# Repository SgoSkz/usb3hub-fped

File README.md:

# usb3hub-fped USB 3 Hub for Programmers &amp; Embedded Developers

## What's wrong with normal USB hubs? **Nothing**. USB hubs have tons of
features like an SD reader, HDMI/DP output (video), EXTRA USB PORTS (shocking),
and sometimes even audio jacks. These are all great features, _but_ I want a
USB hub that has features for embedded programming such as i2c, spi, uart, and
maybe even jtag (prob not). Mainly because I'm tired of having 4 different
devices for dealing with one project.

## Goals
- [ ] Basic USB hub functional
- [ ] SD card reader
- [ ] Embedded programmer stuff functional

## Plan
- 3x USB 3 downstream ports available
- 1x USB 3 downstream reserved for USB 2 hub
- USB 2 hub connects to embedded programming devices and SD reader

## Hardware
- Utilizes the TUSB8041
- Embedded stuff
	- Possibly put an ATmega32u4
		- Easy to program with native USB support
	- Individual IC's for i2c, spi, uart, etc
	- Other IC/uC
- Power management ICs
	- 1v1	->
	- 3v3	->
	- 5v	->
- XTAL selection
	- 24MHz	->

## Software
- Developed in KiCAD :D

## License Here When Chosen
- Ermmm =T

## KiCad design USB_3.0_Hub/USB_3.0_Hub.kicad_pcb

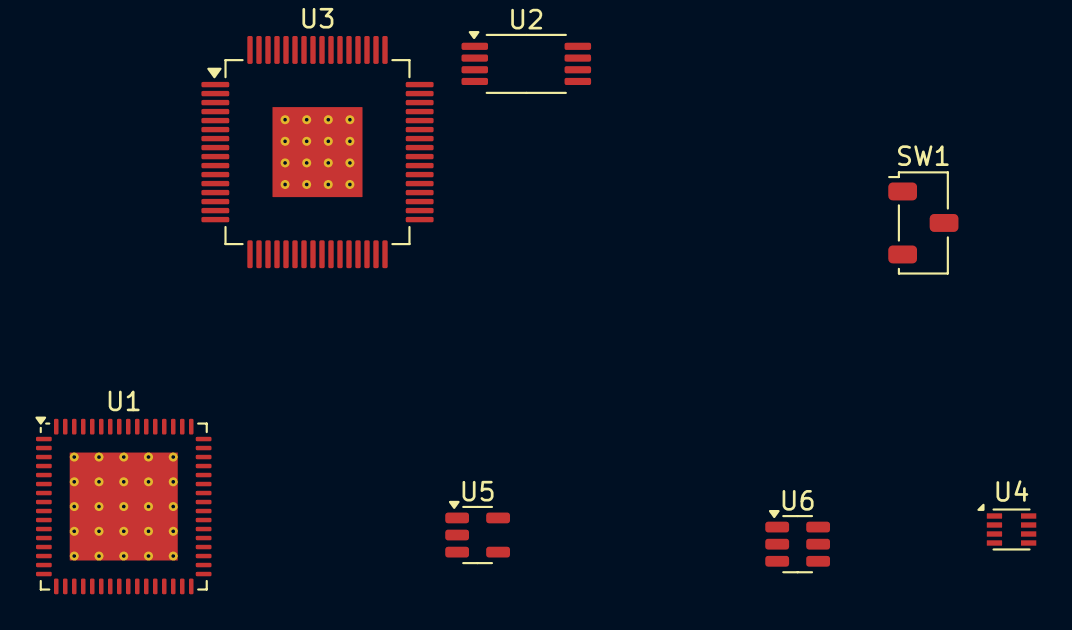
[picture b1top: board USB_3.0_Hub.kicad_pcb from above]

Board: 2 copper layers, 7 parts (0 on the bottom side), 10 nets, no tracks yet.

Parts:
SW1: I2C Selector; Nidec_Copal_CAS-120A
U1: TUSB8041; QFN-64-1EP_9x9mm_P0.5mm_EP6x6mm_ThermalVias
U2: AT24CS04-XHM; TSSOP-8_4.4x3mm_P0.65mm
U3: FT4232H; LQFP-64-1EP_10x10mm_P0.5mm_EP5x5mm_ThermalVias
U4: MAX15062A; DFN-8_2x2mm_P0.5mm
U5: ADP2108AUJ-1.1; TSOT-23-5
U6: 93LCxxBxxOT; SOT-23-6

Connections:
+1V1: U1.5 (VDD), U1.8 (VDD), U1.13 (VDD), U1.21 (VDD), U1.28 (VDD), U1.31 (VDD), U1.51 (VDD), U1.57 (VDD), U5.4 (FB)
+3.3V: U1.16 (VDD33), U1.34 (VDD33), U1.52 (VDD33), U1.63 (VDD33), U2.8 (VCC), U3.50 (VREGIN), U4.4 (FB/Vout), U5.1 (Vin), U5.3 (EN), U6.6 (VCC)
/FTCLK: U3.62 (EECLK), U6.4 (CLK)
/FTCS: U3.63 (EECS), U6.5 (CS)
/FTDATA: U3.61 (EEDATA), U6.3 (DI)
/SMBUSz/SS_SUSPEND: SW1.2 (B), U1.39 (SMBUSz/SS_SUSPEND)
/VCORE: U3.12 (VCORE), U3.37 (VCORE), U3.49 (VREGOUT), U3.64 (VCORE)
/VIO: U3.20 (VCCIO), U3.31 (VCCIO), U3.42 (VCCIO), U3.56 (VCCIO)
GND1: U1.65 (VSS), U2.4 (GND), U3.1 (GND), U3.5 (GND), U3.10 (AGND), U3.11 (GND), U3.13 (TEST), U3.15 (GND), U3.25 (GND), U3.35 (GND), U3.47 (GND), U3.51 (GND), U4.7 (GND), U5.2 (GND), U6.2 (GND)
VCC: U4.1 (VIN), U4.2 (EN/UVLO)

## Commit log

2025-08-14 Fixed file structure
2025-08-14 Added plans
2025-08-14 Updated goals
2025-08-14 Update FeatureList.md
    Added link regarding future VID:PID things
2025-11-14 added stuff
2025-11-15 abruh
2025-11-15 push
